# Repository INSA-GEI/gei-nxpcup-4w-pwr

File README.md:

# GEI NXP Cup — Carte puissance

Dépôt regroupant les fichiers de conception matérielle et logicielle de la carte de puissance du vehicule développé au département Génie Électrique et Informatique (GEI) de l'INSA Toulouse pour la compétition NXP Cup.

La carte de puissance est installée à l'arrière du véhicule. Elle assure la commande des actionneurs et la gestion de plusieurs périphériques du vehicule. Elle est construite autour d'un microcontrôleur **NXP MCXA153**.

## Fonctions de la carte

La carte de puissance assure les fonctions suivantes :

- **Commande des moteurs** de propulsion du véhicule.
- **Commande du servomoteur** de direction.
- **Mesure du niveau de batterie**, afin de surveiller l'alimentation du vehicule.
- **Commande des LED d'éclairage** du véhicule.
- **Connexion de périphériques I²C**.
- **Communication avec la carte principale** basée sur la FRDM-IMX8MP, via le bus I²C et une nappe de liaison.

La carte assure ainsi l'interface entre la carte principale, les actionneurs et les périphériques matériels du véhicule.

## Organisation du dépôt

Le dépôt est organisé en deux répertoires principaux.

| Répertoire | Contenu |
|---|---|
| [`hardware/`](hardware/) | Projet de conception électronique sous KiCad et nomenclature des composants (BOM) |
| [`software/`](software/) | Projet MCUXpresso IDE contenant le firmware en langage C destiné au microcontrôleur MCXA153 |

## 1. Conception matérielle — `hardware/`

Le répertoire `hardware/` contient les fichiers du projet KiCad utilisés pour concevoir la carte électronique de puissance.

Ils permettent notamment de consulter et de modifier le schéma électronique et le circuit imprimé (PCB).

La nomenclature des composants (**BOM — Bill of Materials**) est également fournie afin d'identifier les composants nécessaires à la fabrication de la carte.

### Outils nécessaires

- [KiCad](https://www.kicad.org/) : consultation et modification du schéma électronique et du circuit imprimé.
- Un outil de tableur peut être utilisé pour consulter la BOM, selon le format du fichier fourni.

Avant toute fabrication ou modification matérielle, vérifier la cohérence entre le schéma, le PCB, la nomenclature et la révision de carte utilisée sur le véhicule.

## 2. Firmware — `software/`

Le répertoire `software/` contient le projet **MCUXpresso IDE** et le code source C exécuté par le microcontrôleur NXP MCXA153.

Ce firmware assure les fonctions de commande de la carte de puissance et la communication avec la carte principale via le bus I²C.

### Outils nécessaires

- [MCUXpresso IDE](https://www.nxp.com/mcuxpresso) — version **26.2 ou supérieure**.
- Les composants logiciels et le SDK compatibles avec le projet et le microcontrôleur MCXA153.
- Une interface de programmation et de débogage compatible avec le matériel utilisé.

### Ouverture et compilation du projet

1. Installer MCUXpresso IDE dans une version compatible avec le projet.
2. Ouvrir l'environnement de développement et sélectionner un espace de travail (*workspace*).
3. Importer le projet présent dans le répertoire `software/`.
4. Vérifier que les composants logiciels et le SDK requis sont disponibles.
5. Compiler le projet et corriger les éventuelles erreurs de configuration.
6. Programmer le microcontrôleur avec le firmware compilé, en utilisant une interface de programmation compatible.

Les modalités exactes de programmation dépendent de la configuration matérielle et de l'interface de débogage utilisée.

## Ressources

- [NXP MCXA153 — informations produit et documentation](https://www.nxp.com/products/MCXA153)
- [MCUXpresso — environnement de développement NXP](https://www.nxp.com/mcuxpresso)
- [KiCad — logiciel de conception électronique](https://www.kicad.org/)

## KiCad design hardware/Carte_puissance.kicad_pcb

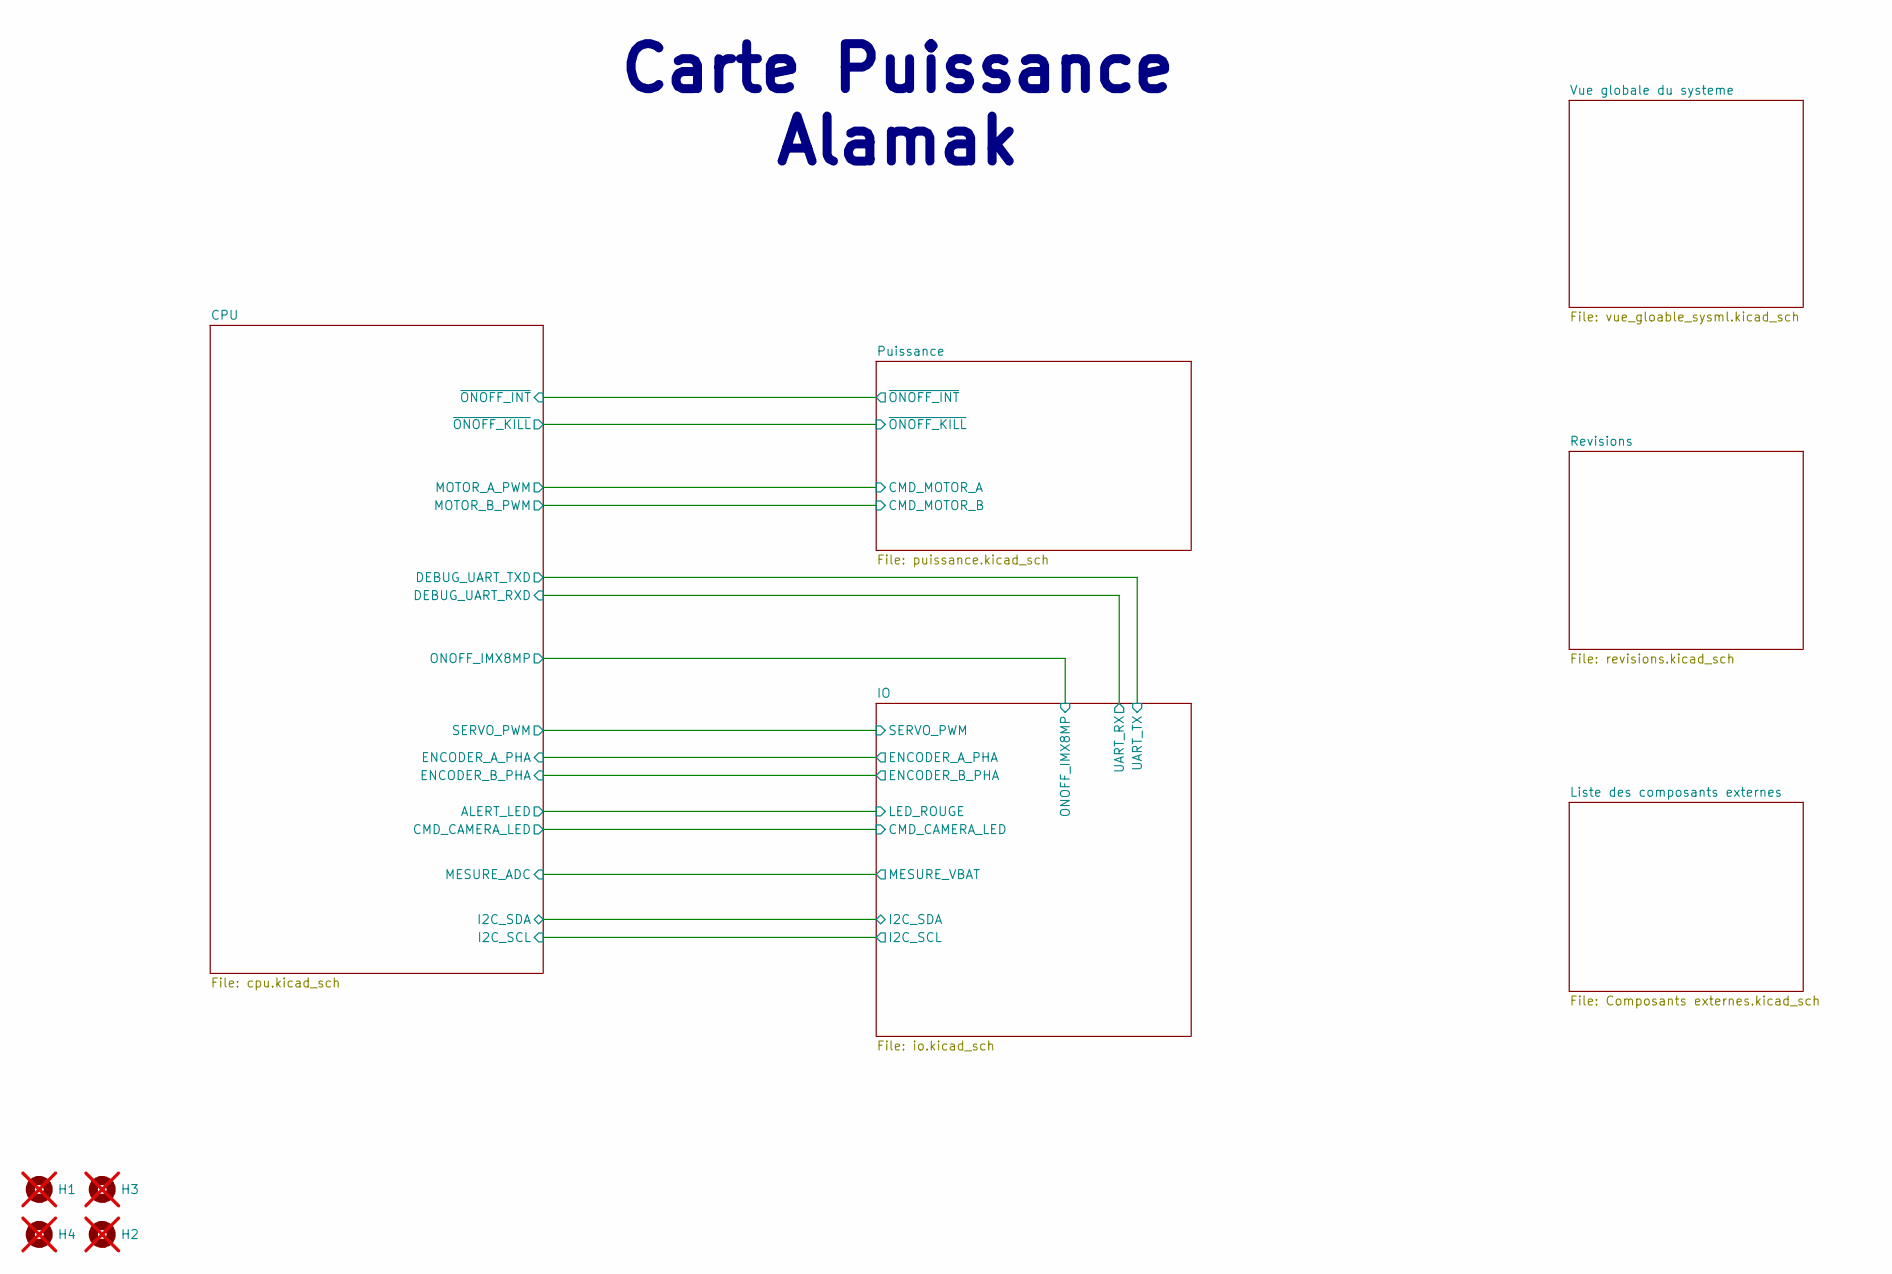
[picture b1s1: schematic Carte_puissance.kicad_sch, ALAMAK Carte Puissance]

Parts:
H1, H2, H3, H4: MountingHole; MountingHole_3.2mm_M3; not fitted

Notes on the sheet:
Carte Puissance Alamak

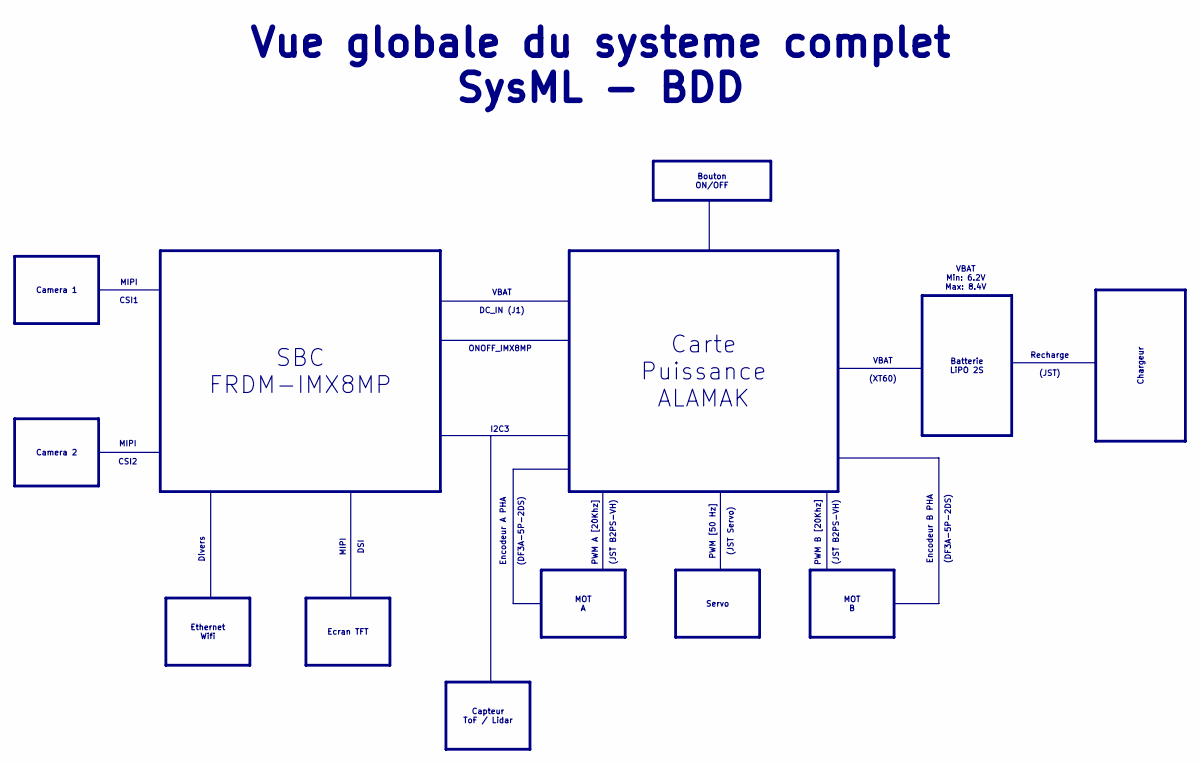
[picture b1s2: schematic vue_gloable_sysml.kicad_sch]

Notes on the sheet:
Chargeur
Servo
MOT A
MOT B
Ecran TFT
Batterie LiPO 2S
Capteur ToF / Lidar
Ethernet Wifi
SBC FRDM-IMX8MP
Camera 2
Camera 1
Carte Puissance ALAMAK
Bouton ON/OFF
PWM [50 Hz] (JST Servo)
VBAT Min: 6.2V Max: 8.4V
Vue globale du systeme complet SysML - BDD
Encodeur A PHA (DF3A-5P-2DS)
ONOFF_IMX8MP
PWM A [20Khz] (JST B2PS-VH)
MIPI CSI1
VBAT DC_IN (J1)
Divers
Recharge (JST)
VBAT (XT60)
Encodeur B PHA (DF3A-5P-2DS)
I2C3
MIPI CSI2
PWM B [20Khz] (JST B2PS-VH)
MIPI DSI

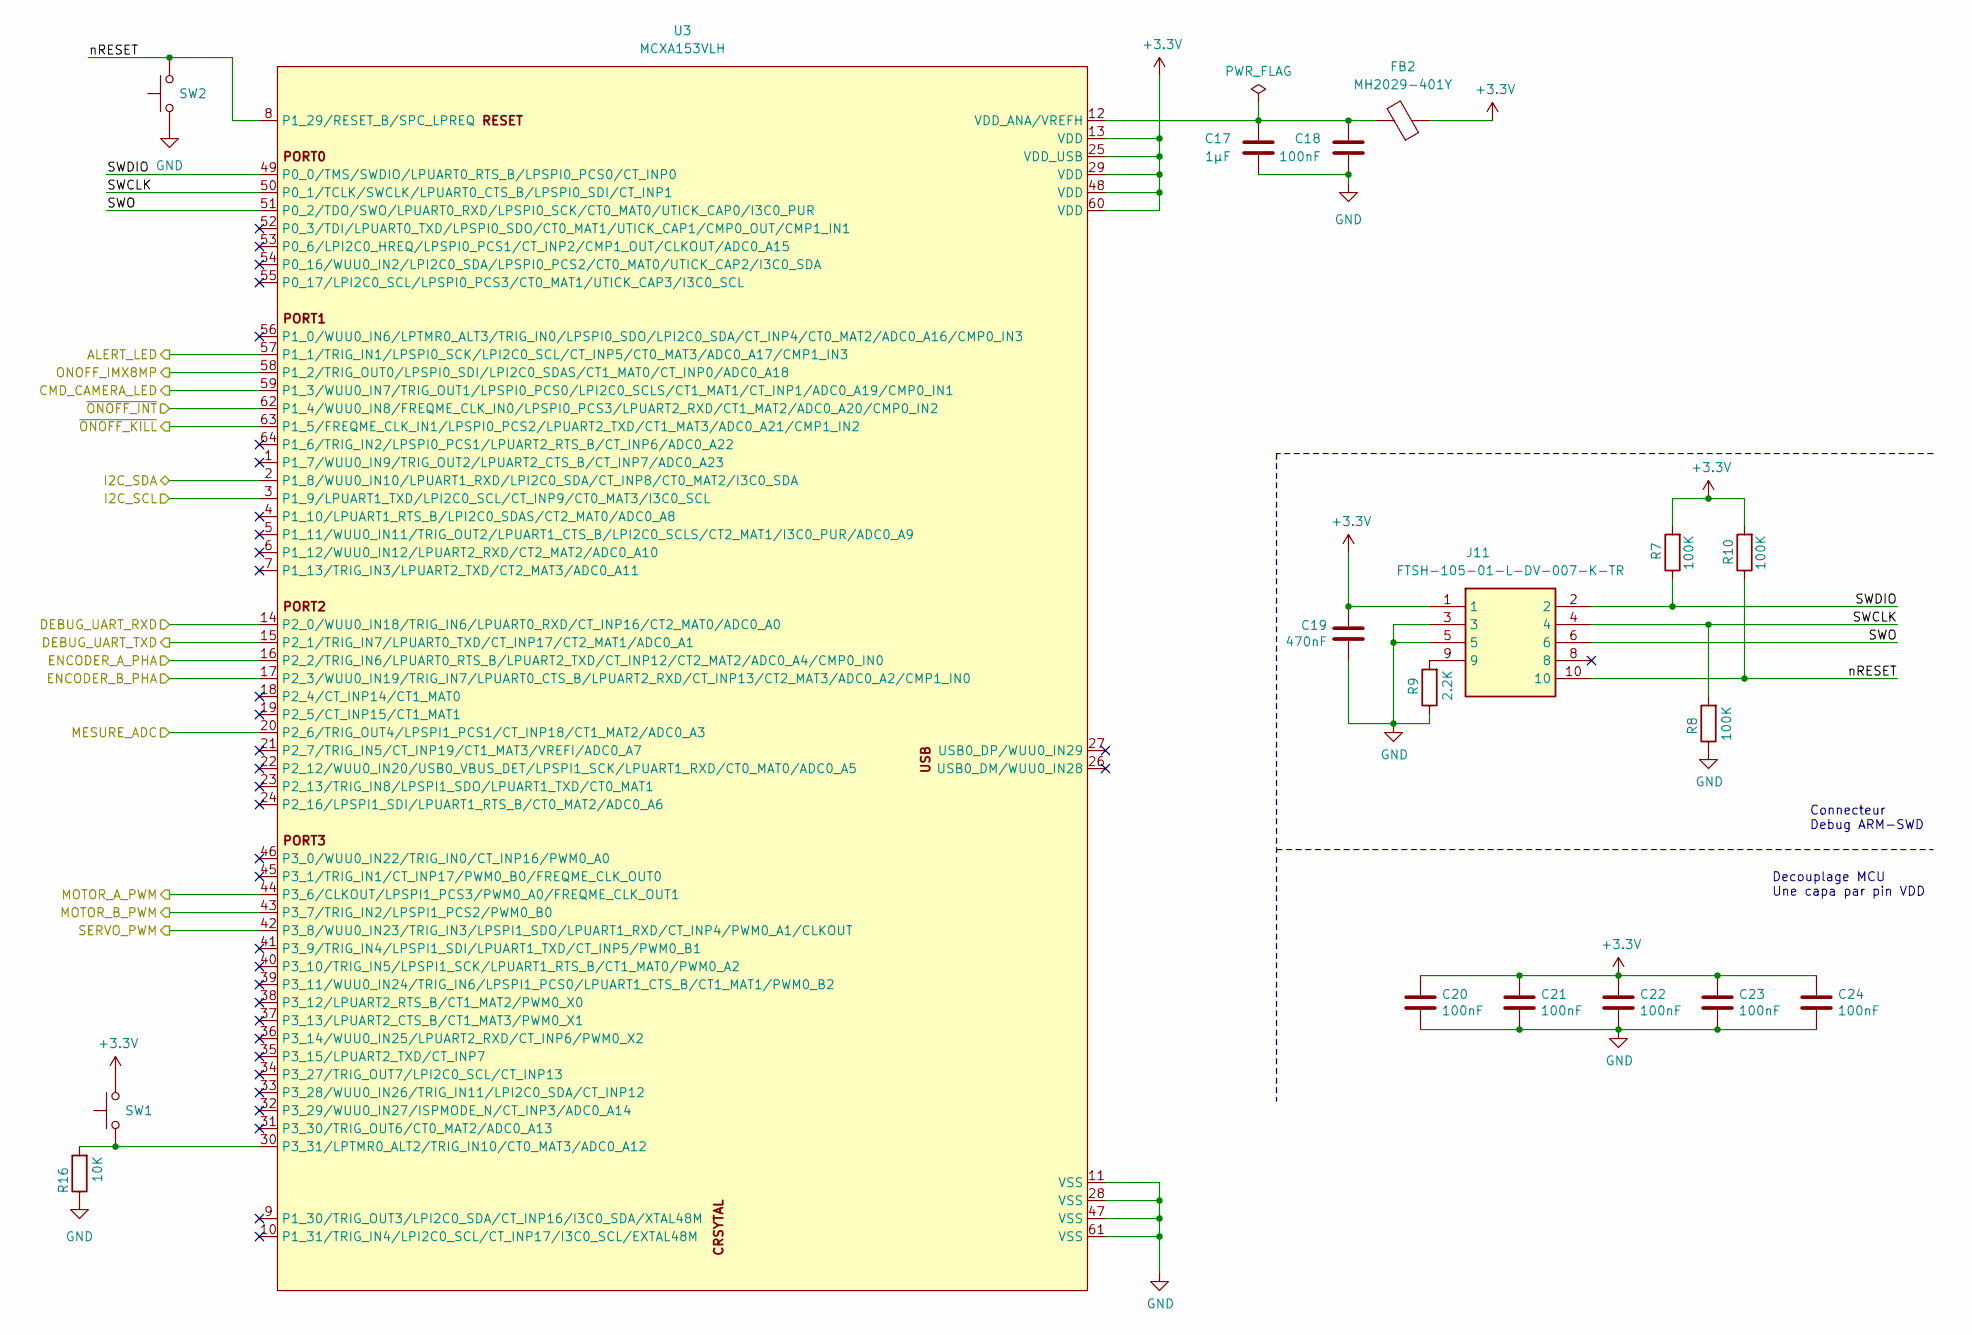
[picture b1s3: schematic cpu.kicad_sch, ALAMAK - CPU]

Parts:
C17: 1µF; C_0805_2012Metric; Part Number CL21B105KBFNNNF
C18, C20, C21, C22, C23, C24: 100nF; C_0805_2012Metric; Part Number CL21B104KBFNNNG
C19: 470nF; C_0805_2012Metric; Part Number CL21B474KBFNNNG
FB2: MH2029-401Y; C_0805_2012Metric_Pad1.18x1.45mm_HandSolder; Part Number MH2029-401Y
J11: FTSH-105-01-L-DV-007-K-TR; FTSH10501LDV007KTR; Part Number FTSH-105-01-L-DV-007-K-TR
R7, R8, R10: 100K; R_0805_2012Metric; Part Number RT0805FRE10100KL
R9: 2.2K; R_0805_2012Metric; Part Number RT0805FRE132K2L
R16: 10K; R_0805_2012Metric; Part Number RCA080510K0JNEASR
SW1, SW2: EVQ-P2602M; SW_SPST_EVQP2; Part Number EVQ-P2602M
U3: MCXA153VLH; LQFP-64_10x10mm_P0.5mm; Part Number MCXA153VLH

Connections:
+3.3V: C19.1, C20.1, C21.1, C22.1, C23.1, C24.1, FB2.1, J11.1, R7.2, R10.2, SW1.2, U3.13 (VDD), U3.25 (VDD_USB), U3.29 (VDD), U3.48 (VDD), U3.60 (VDD); also elsewhere on the board
/CPU/ALERT_LED: U3.57 (P1_1/TRIG_IN1/LPSPI0_SCK/LPI2C0_SCL/CT_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); also elsewhere on the board
/CPU/CMD_CAMERA_LED: U3.59 (P1_3/WUU0_IN7/TRIG_OUT1/LPSPI0_PCS0/LPI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); also elsewhere on the board
/CPU/DEBUG_UART_RXD: U3.14 (P2_0/WUU0_IN18/TRIG_IN6/LPUART0_RXD/CT_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); also elsewhere on the board
/CPU/DEBUG_UART_TXD: U3.15 (P2_1/TRIG_IN7/LPUART0_TXD/CT_INP17/CT2_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); also elsewhere on the board
/CPU/ENCODER_A_PHA: U3.16 (P2_2/TRIG_IN6/LPUART0_RTS_B/LPUART2_TXD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); also elsewhere on the board
/CPU/ENCODER_B_PHA: U3.17 (P2_3/WUU0_IN19/TRIG_IN7/LPUART0_CTS_B/L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); also elsewhere on the board
/CPU/I2C_SCL: U3.3 (P1_9/LPUART1_TXD/LPI2C0_SCL/CT_INP9/CT0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); also elsewhere on the board
/CPU/I2C_SDA: U3.2 (P1_8/WUU0_IN10/LPUART1_RXD/LPI2C0_SDA/C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); also elsewhere on the board
/CPU/MESURE_ADC: U3.20 (P2_6/TRIG_OUT4/LPSPI1_PCS1/CT_INP18/CT1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); also elsewhere on the board
/CPU/MOTOR_A_PWM: U3.44 (P3_6/CLKOUT/LPSPI1_PCS3/PWM0_A0/FREQME_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); also elsewhere on the board
/CPU/MOTOR_B_PWM: U3.43 (P3_7/TRIG_IN2/LPSPI1_PCS2/PWM0_B0); also elsewhere on the board
/CPU/ONOFF_IMX8MP: U3.58 (P1_2/TRIG_OUT0/LPSPI0_SDI/LPI2C0_SDAS/C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); also elsewhere on the board
/CPU/SERVO_PWM: U3.42 (P3_8/WUU0_IN23/TRIG_IN3/LPSPI1_SDO/LPUA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); also elsewhere on the board
/CPU/SWCLK: J11.4, R8.2, U3.50 (P0_1/TCLK/SWCLK/LPUART0_CTS_B/LPSPI0_SD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)
/CPU/SWDIO: J11.2, R7.1, U3.49 (P0_0/TMS/SWDIO/LPUART0_RTS_B/LPSPI0_PCS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)
/CPU/SWO: J11.6, U3.51 (P0_2/TDO/SWO/LPUART0_RXD/LPSPI0_SCK/CT0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)
/CPU/nRESET: J11.10, R10.1, SW2.2, U3.8 (P1_29/RESET_B/SPC_LPREQ)
/CPU/~ONOFF_INT: U3.62 (P1_4/WUU0_IN8/FREQME_CLK_IN0/LPSPI0_PCS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); also elsewhere on the board
/CPU/~ONOFF_KILL: U3.63 (P1_5/FREQME_CLK_IN1/LPSPI0_PCS2/LPUART2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); also elsewhere on the board
GND: C17.2, C18.2, C19.2, C20.2, C21.2, C22.2, C23.2, C24.2, J11.3, J11.5, R8.1, R9.1, R16.1, SW2.1, U3.11 (VSS), U3.28 (VSS), U3.47 (VSS), U3.61 (VSS); also elsewhere on the board
unnamed: J11.9, R9.2
unnamed: R16.2, SW1.1, U3.30 (P3_31/LPTMR0_ALT2/TRIG_IN10/CT0_MAT3/AD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)
unnamed: C17.1, C18.1, FB2.2, U3.12 (VDD_ANA/VREFH)

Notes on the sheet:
Decouplage MCU Une capa par pin VDD
Connecteur Debug ARM-SWD

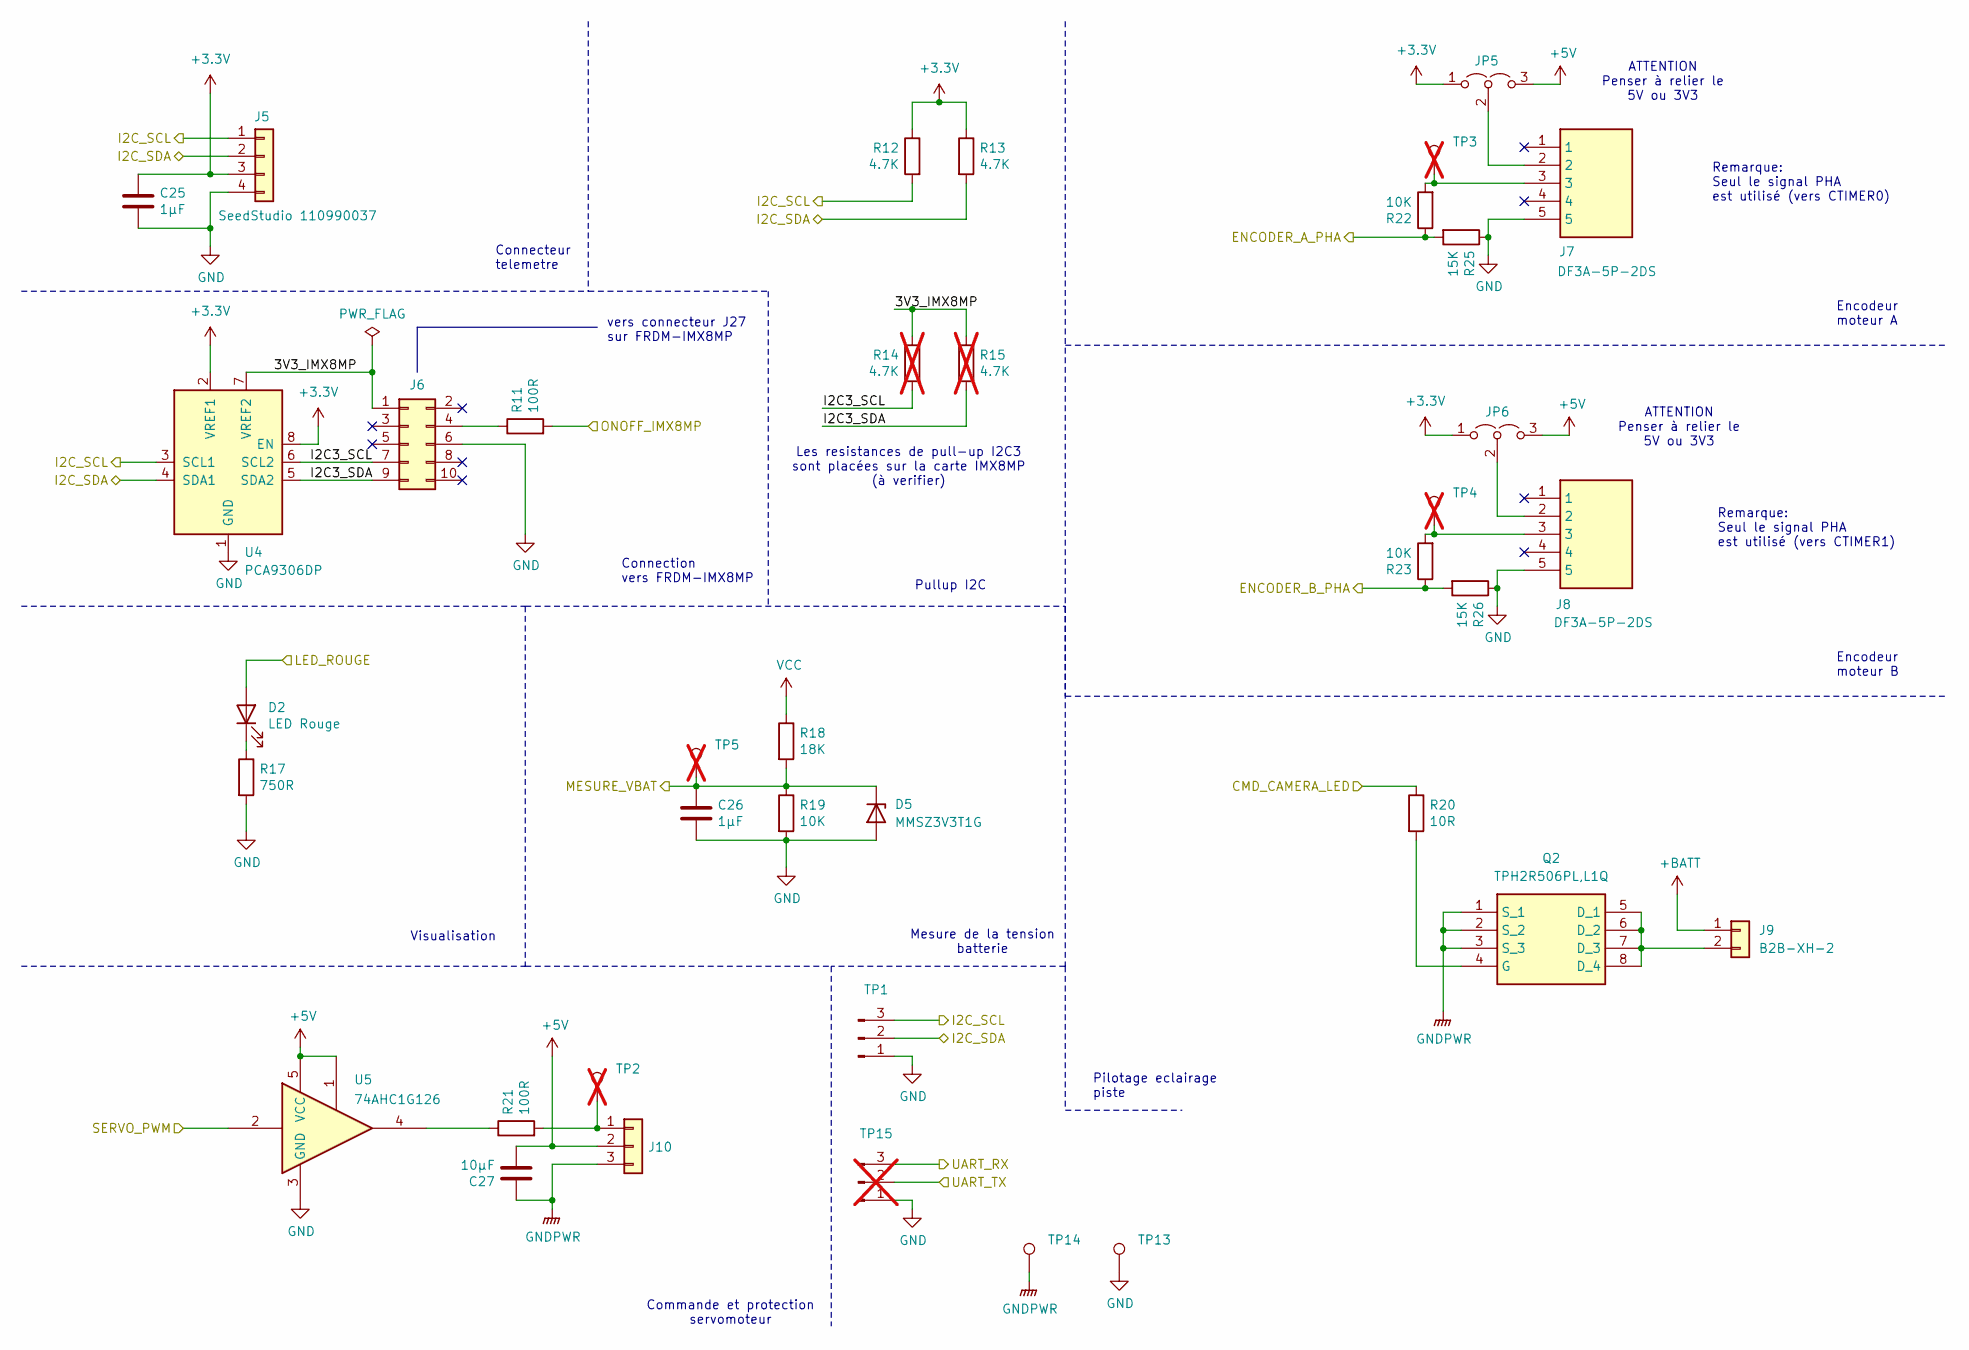
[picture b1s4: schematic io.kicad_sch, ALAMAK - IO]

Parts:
C25, C26: 1µF; C_0805_2012Metric; Part Number CL21B105KBFNNNF
C27: 10µF; C_0805_2012Metric; Part Number CGA4J1X7S1E106K125AE
D2: LED Rouge; LED_0805_2012Metric; Part Number APTD2012LSURCK
D5: MMSZ3V3T1G; D_SOD-123; Part Number MMSZ3V3T1G
J5: SeedStudio 110990037; SEEED_110990037; Part Number 110990037
J6: 72454-010VLF; IDC-Header_2x05_P2.54mm_Vertical_SMD; Part Number 72454-010VLF
J7, J8: DF3A-5P-2DS; SHDRRA5W60P0X200_1X5_1200X720X530P; Part Number DF3A-5P-2DS
J9: B2B-XH-2; JST_XH_B2B-XH-A_1x02_P2.50mm_Vertical; Part Number B2B-XH-2(LF)(SN)
J10: Cable Servomoteur JST; SolderWire-0.5sqmm_1x03_P4.8mm_D0.9mm_OD2.3mm; Part Number Cable JST Servo
JP5, JP6: Jumper_3_Open; SolderJumper-3_P1.3mm_Open_RoundedPad1.0x1.5mm
Q2: TPH2R506PL,L1Q; SOP-8_3.76x4.96mm_P1.27mm; Part Number TPH2R506PL,L1Q
R11, R21: 100R; R_0805_2012Metric; Part Number RT0805DRE07100RL
R12, R13: 4.7K; R_0805_2012Metric; Part Number RK73H2ATTD4701F
R14, R15: 4.7K; R_0805_2012Metric; Part Number RK73H2ATTD4701F; not fitted
R17: 750R; R_0805_2012Metric; Part Number RT0805BRD07750RL
R18: 18K; R_0805_2012Metric; Part Number RT0805FRE0718KL
R19, R22, R23: 10K; R_0805_2012Metric; Part Number RCA080510K0JNEASR
R20: 10R; R_0805_2012Metric; Part Number RT0805FRE1310RL
R25, R26: 15K; R_0805_2012Metric; Part Number RT0805DRE0715KL
TP1: TestPoint; PinHeader_1x03_P2.54mm_Vertical
TP2, TP3, TP4, TP5: TestPoint; PinHeader_1x01_P2.54mm_Vertical; not fitted
TP13, TP14: TestPoint; PinHeader_1x01_P2.54mm_Vertical
TP15: TestPoint; PinHeader_1x03_P2.54mm_Vertical; not fitted
U4: PCA9306DP; TSSOP-8_3x3mm_P0.65mm; Part Number PCA9306DP,118
U5: 74AHC1G126; SOT-23-5; Part Number SN74AHC1G126DBVR

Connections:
+3.3V: C25.1, J5.3, JP5.1 (A), JP6.1 (A), R12.1, R13.1, U4.2 (VREF1), U4.8 (EN); also elsewhere on the board
+5V: C27.2, J10.2, JP5.3 (B), JP6.3 (B), U5.1, U5.5 (VCC); also elsewhere on the board
+BATT: J9.1; also elsewhere on the board
/CPU/ALERT_LED: D2.2 (A); also elsewhere on the board
/CPU/CMD_CAMERA_LED: R20.1; also elsewhere on the board
/CPU/DEBUG_UART_RXD: TP15.3; also elsewhere on the board
/CPU/DEBUG_UART_TXD: TP15.2; also elsewhere on the board
/CPU/ENCODER_A_PHA: R22.1, R25.2; also elsewhere on the board
/CPU/ENCODER_B_PHA: R23.1, R26.2; also elsewhere on the board
/CPU/I2C_SCL: J5.1, R12.2, TP1.3, U4.3 (SCL1); also elsewhere on the board
/CPU/I2C_SDA: J5.2, R13.2, TP1.2, U4.4 (SDA1); also elsewhere on the board
/CPU/MESURE_ADC: C26.1, D5.1 (K), R18.2, R19.1, TP5.1; also elsewhere on the board
/CPU/ONOFF_IMX8MP: R11.2; also elsewhere on the board
/CPU/SERVO_PWM: U5.2; also elsewhere on the board
/IO/3V3_IMX8MP: J6.1, R14.1, R15.1, U4.7 (VREF2)
/IO/I2C3_SCL: J6.7, R14.2, U4.6 (SCL2)
/IO/I2C3_SDA: J6.9, R15.2, U4.5 (SDA2)
GND: C25.2, C26.2, D5.2 (A), J5.4, J6.6, J7.5, J8.5, R17.2, R19.2, R25.1, R26.1, TP1.1, TP13.1, TP15.1, U4.1 (GND), U5.3 (GND); also elsewhere on the board
GNDPWR: C27.1, J10.3, Q2.1 (S_1), Q2.2 (S_2), Q2.3 (S_3), TP14.1; also elsewhere on the board
unnamed: D2.1 (K), R17.1
unnamed: J6.4, R11.1
unnamed: J7.3, R22.2, TP3.1
unnamed: J8.3, R23.2, TP4.1
unnamed: J9.2, Q2.5 (D_1), Q2.6 (D_2), Q2.7 (D_3), Q2.8 (D_4)
unnamed: J10.1, R21.2, TP2.1
unnamed: J7.2, JP5.2 (C)
unnamed: J8.2, JP6.2 (C)
unnamed: Q2.4 (G), R20.2
unnamed: R21.1, U5.4
VCC: R18.1; also elsewhere on the board

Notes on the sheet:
Connecteur telemetre
ATTENTION Penser à relier le 5V ou 3V3
Mesure de la tension batterie
Remarque: Seul le signal PHA est utilisé (vers CTIMER0)
Visualisation
Connection vers FRDM-IMX8MP
Encodeur moteur B
Pilotage eclairage piste
vers connecteur J27 sur FRDM-IMX8MP
Les resistances de pull-up I2C3 sont placées sur la carte IMX8MP (à verifier)
Commande et protection servomoteur
Encodeur moteur A
Remarque: Seul le signal PHA est utilisé (vers CTIMER1)
Pullup I2C

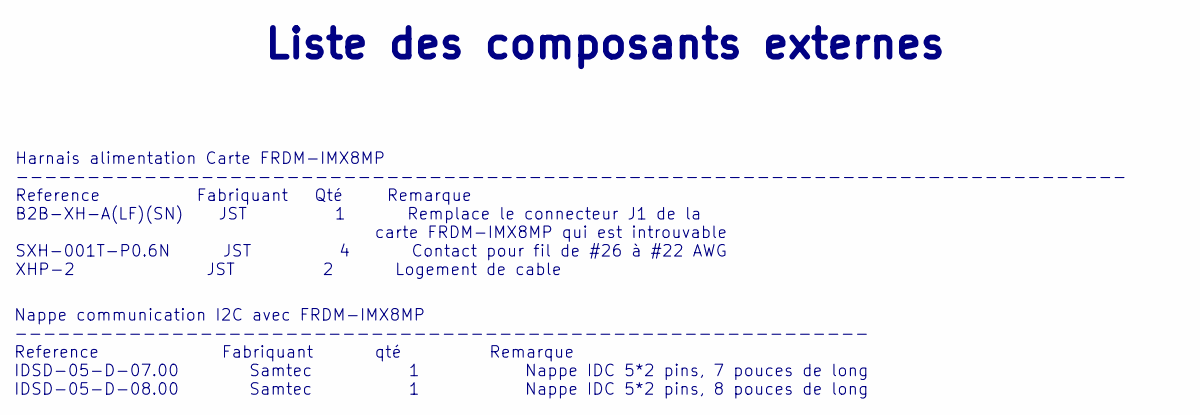
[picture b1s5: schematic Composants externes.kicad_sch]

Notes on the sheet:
Harnais alimentation Carte FRDM-IMX8MP ------------------------------------------------------------------------------ Reference Fabriquant Qté Remarque B2B-XH-A(LF)(SN) JST 1 Remplace le connecteur J1 de la carte FRDM-IMX8MP qui est introuvable SXH-001T-P0.6N JST 4 Contact pour fil de #26 à #22 AWG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
Nappe communication I2C avec FRDM-IMX8MP ------------------------------------------------------------ Reference Fabriquant qté Remarque IDSD-05-D-07.00 Samtec 1 Nappe IDC 5*2 pins, 7 pouces de long IDSD-05-D-08.00 Samtec 1 Nappe IDC 5*2 pins, 8 pouces de long
Liste des composants externes

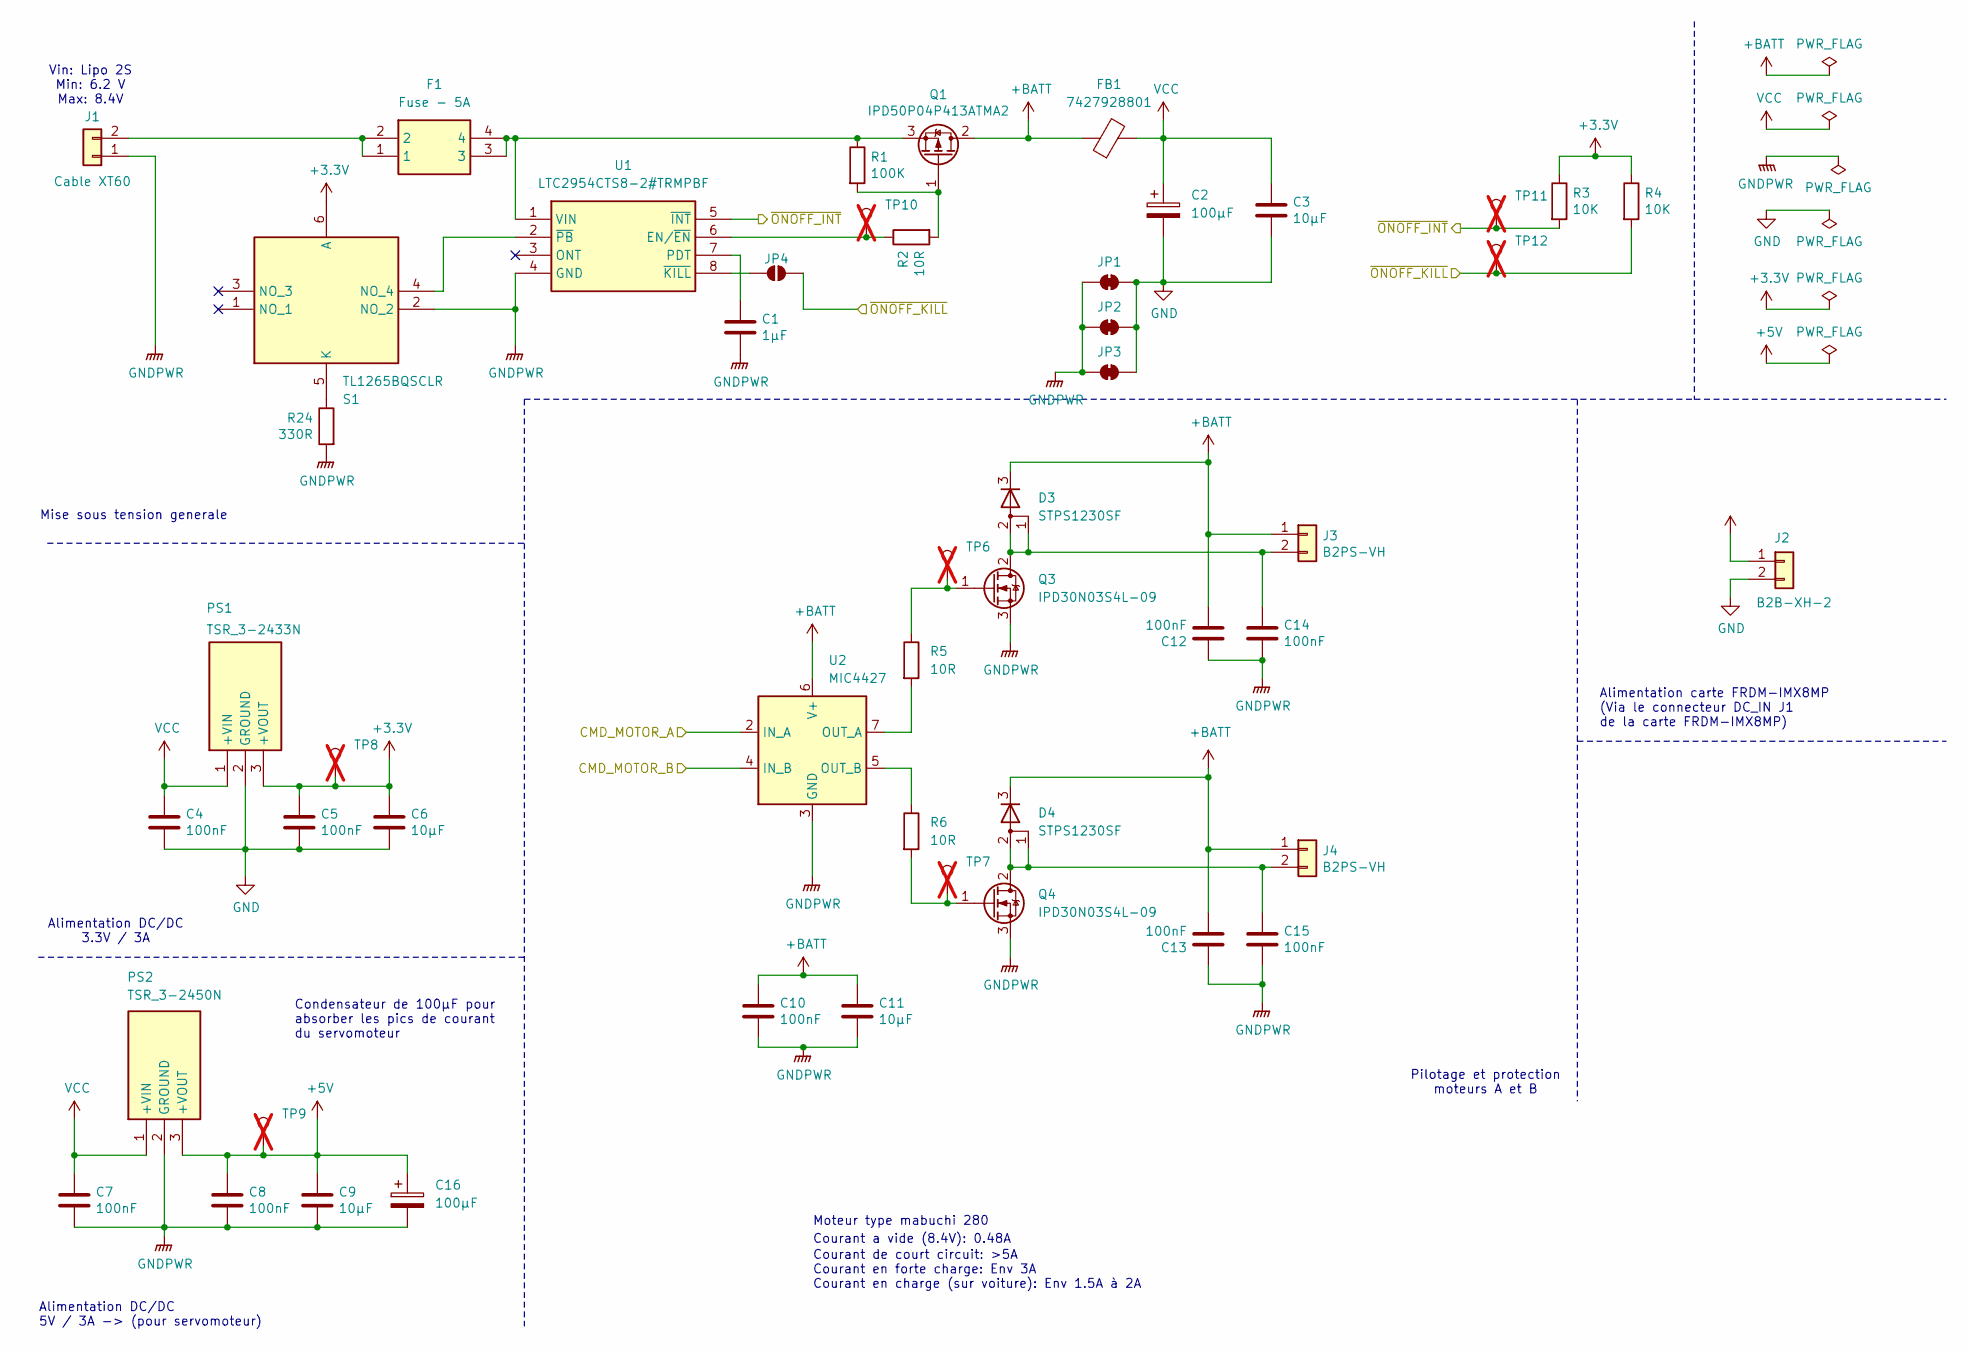
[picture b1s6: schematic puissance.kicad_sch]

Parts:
C1: 1µF; C_0805_2012Metric; Part Number CL21B105KBFNNNF
C2, C16: 100µF; CP_Elec_10x10; Part Number EMVH500ARA101MJA0G
C3, C6, C9, C11: 10µF; C_0805_2012Metric; Part Number CGA4J1X7S1E106K125AE
C4, C5, C7, C8, C10, C12, C13, C14, C15: 100nF; C_0805_2012Metric; Part Number CL21B104KBFNNNG
D3, D4: STPS1230SF; TO-277A; Part Number STPS1230SF
F1: Fuse - 5A; 3568; Part Number 3568
FB1: 7427928801; C_2220_5750Metric; Part Number 7427928801
J1: Cable XT60; Battery_Pads; Part Number Cable batterie XT60
J2: B2B-XH-2; JST_XH_B2B-XH-A_1x02_P2.50mm_Vertical; Part Number B2B-XH-2(LF)(SN)
J3, J4: B2PS-VH; JST_VH_B2PS-VH_1x02_P3.96mm_Horizontal; Part Number B2PS-VH(LF)(SN)
JP1, JP2, JP3: SolderJumper_2_Bridged; SolderJumper-2_P1.3mm_Bridged2Bar_RoundedPad1.0x1.5mm
JP4: SolderJumper_2_Open; SolderJumper-2_P1.3mm_Open_RoundedPad1.0x1.5mm
PS1: TSR_3-2433N; TSR324xxN; Part Number TSR_3-2433N
PS2: TSR_3-2450N; TSR324xxN; Part Number TSR_3-2450N
Q1: IPD50P04P413ATMA2; TO-252-2; Part Number IPD50P04P413ATMA2
Q3, Q4: IPD30N03S4L-09; TO-252-2; Part Number IPD30N03S4L-09
R1: 100K; R_0805_2012Metric; Part Number RT0805FRE10100KL
R2, R5, R6: 10R; R_0805_2012Metric; Part Number RT0805FRE1310RL
R3, R4: 10K; R_0805_2012Metric; Part Number RCA080510K0JNEASR
R24: 330R; R_0805_2012Metric; Part Number RT0805DRD07330RL
S1: TL1265BQSCLR; Mouser Part Number 612-TL1265BQSCLR
TP6, TP7, TP8, TP9, TP10, TP11, TP12: TestPoint; PinHeader_1x01_P2.54mm_Vertical; not fitted
U1: LTC2954CTS8-2#TRMPBF; SOT-23-8; Part Number LTC2954CTS8-2#TRPBF
U2: MIC4427; SO-8_3.9x4.9mm_P1.27mm; Part Number MIC4427ZM

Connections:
+3.3V: C5.1, C6.1, PS1.3 (+VOUT), R3.1, R4.1, S1.6 (A), TP8.1; also elsewhere on the board
+5V: C8.1, C9.1, C16.1, PS2.3 (+VOUT), TP9.1; also elsewhere on the board
+BATT: C10.1, C11.1, C12.2, C13.2, D3.3 (K), D4.3 (K), FB1.1, J3.1, J4.1, Q1.2 (D), U2.6 (V+); also elsewhere on the board
/CPU/MOTOR_A_PWM: U2.2 (IN_A); also elsewhere on the board
/CPU/MOTOR_B_PWM: U2.4 (IN_B); also elsewhere on the board
/CPU/~ONOFF_INT: R3.2, TP11.1, U1.5 (~INT); also elsewhere on the board
/CPU/~ONOFF_KILL: JP4.2 (B), R4.2, TP12.1; also elsewhere on the board
GND: C2.2, C3.2, C4.2, C5.2, C6.2, J2.2, JP1.2 (B), JP2.2 (B), JP3.2 (B), PS1.2 (GROUND); also elsewhere on the board
GNDPWR: C1.2, C7.2, C8.2, C9.2, C10.2, C11.2, C12.1, C13.1, C14.2, C15.2, C16.2, J1.1, JP1.1 (A), JP2.1 (A), JP3.1 (A), PS2.2 (GROUND), Q3.3 (S), Q4.3 (S), R24.2, S1.2 (NO_2), U1.4 (GND), U2.3 (GND); also elsewhere on the board
unnamed: F1.1, F1.2, J1.2
unnamed: C14.1, D3.1 (A), D3.2 (A), J3.2, Q3.2 (D)
unnamed: C15.1, D4.1 (A), D4.2 (A), J4.2, Q4.2 (D)
unnamed: JP4.1 (A), U1.8 (~KILL)
unnamed: Q1.1 (G), R1.2, R2.2
unnamed: F1.3, F1.4, Q1.3 (S), R1.1, U1.1 (VIN)
unnamed: Q3.1 (G), R5.1, TP6.1
unnamed: Q4.1 (G), R6.2, TP7.1
unnamed: R24.1, S1.5 (K)
unnamed: S1.4 (NO_4), U1.2 (~PB)
unnamed: R2.1, TP10.1, U1.6 (EN/~EN)
unnamed: C1.1, U1.7 (PDT)
unnamed: R5.2, U2.7 (OUT_A)
unnamed: R6.1, U2.5 (OUT_B)
VCC: C2.1, C3.1, C4.1, C7.1, FB1.2, J2.1, PS1.1 (+VIN), PS2.1 (+VIN); also elsewhere on the board

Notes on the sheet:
Alimentation DC/DC 3.3V / 3A
Alimentation carte FRDM-IMX8MP (Via le connecteur DC_IN J1 de la carte FRDM-IMX8MP)
Mise sous tension generale
Vin: Lipo 2S Min: 6.2 V Max: 8.4V
Courant de court circuit: >5A Courant en forte charge: Env 3A Courant en charge (sur voiture): Env 1.5A à 2A
Condensateur de 100µF pour absorber les pics de courant du servomoteur
Alimentation DC/DC 5V / 3A -> (pour servomoteur)
Moteur type mabuchi 280
Courant a vide (8.4V): 0.48A
Pilotage et protection moteurs A et B

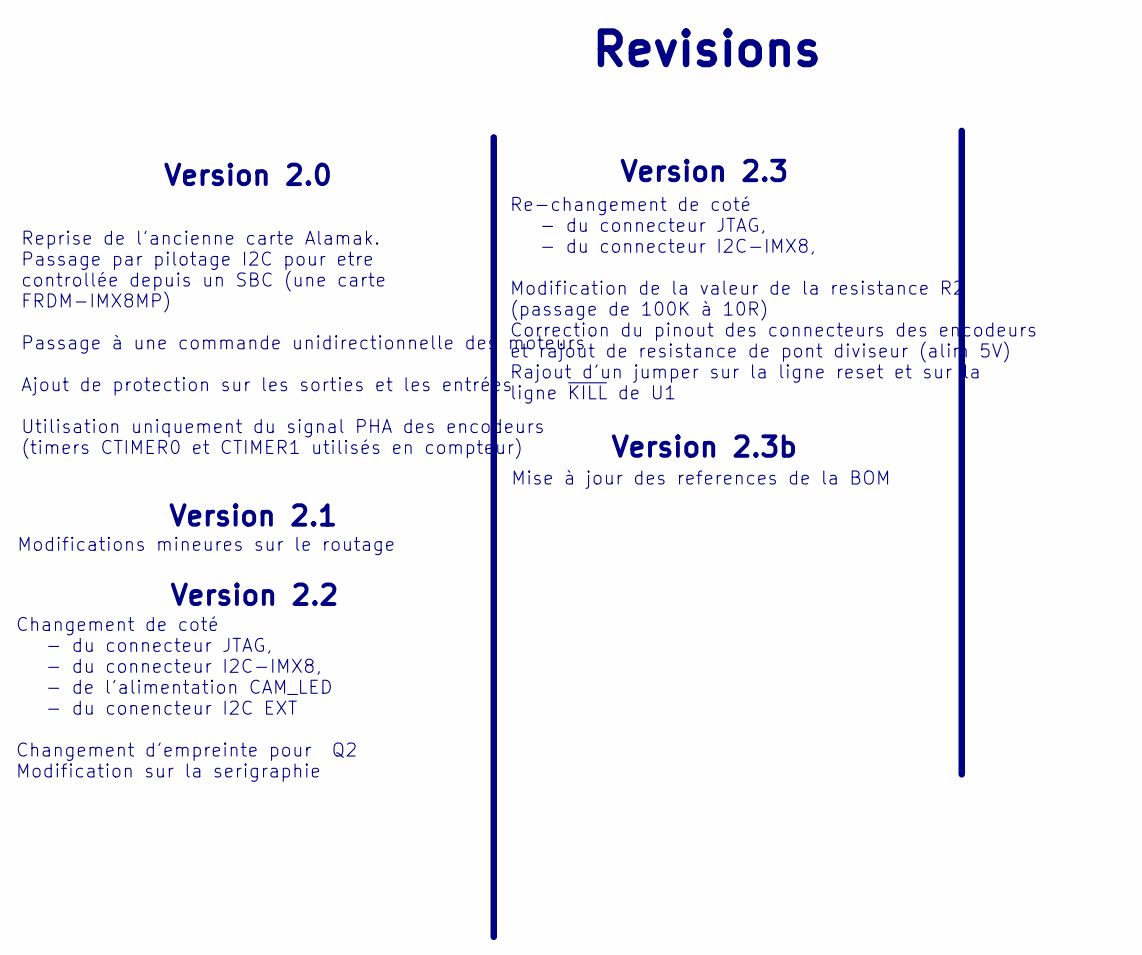
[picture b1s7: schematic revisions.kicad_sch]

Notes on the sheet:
Version 2.2
Mise à jour des references de la BOM
Version 2.3b
Version 2.1
Modifications mineures sur le routage
Version 2.3
Re-changement de coté - du connecteur JTAG, - du connecteur I2C-IMX8, Modification de la valeur de la resistance R2 (passage de 100K à 10R) Correction du pinout des connecteurs des encodeurs et rajout de resistance de pont diviseur (alim 5V) Rajout d'un jumper sur la ligne reset et sur la ligne ~{K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
Reprise de l'ancienne carte Alamak. Passage par pilotage I2C pour etre controllée depuis un SBC (une carte FRDM-IMX8MP) Passage à une commande unidirectionnelle des moteurs Ajout de protection sur les sorties et les entrées Utilisation uniquement du signal PHA des encodeurs (timers CTIMER0 et CTIME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
Version 2.0
Changement de coté - du connecteur JTAG, - du connecteur I2C-IMX8, - de l'alimentation CAM_LED - du conencteur I2C EXT Changement d'empreinte pour Q2 Modification sur la serigraphie
Revisions

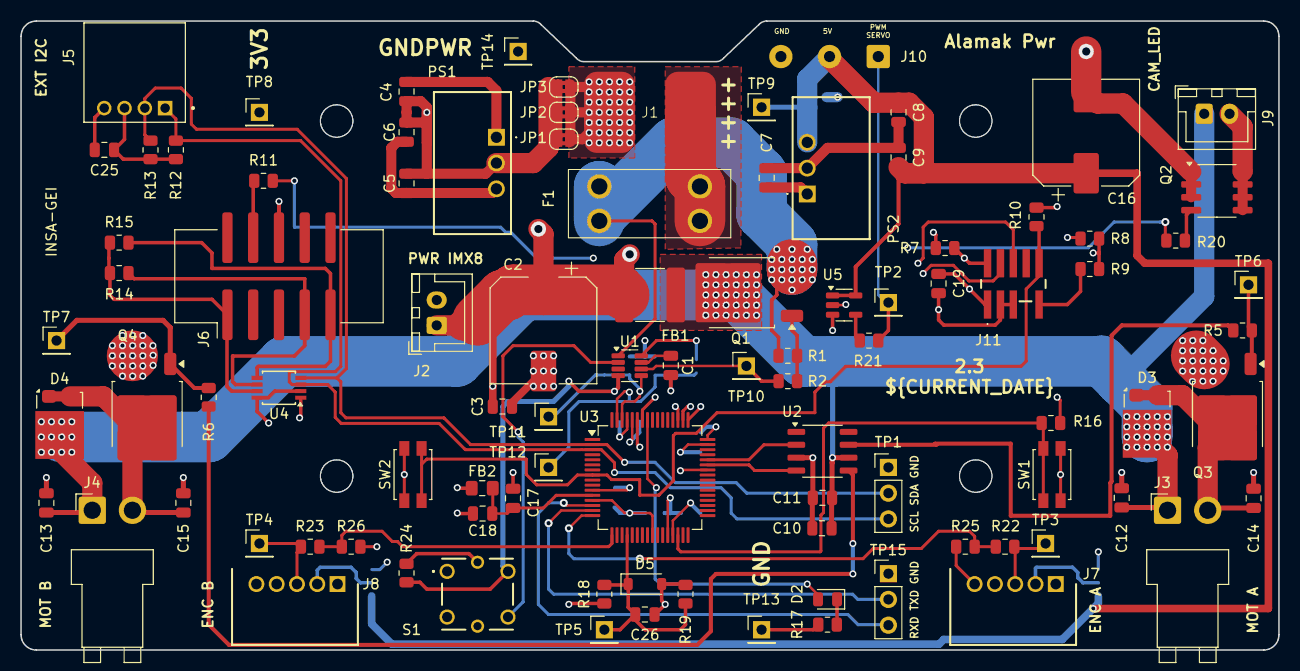
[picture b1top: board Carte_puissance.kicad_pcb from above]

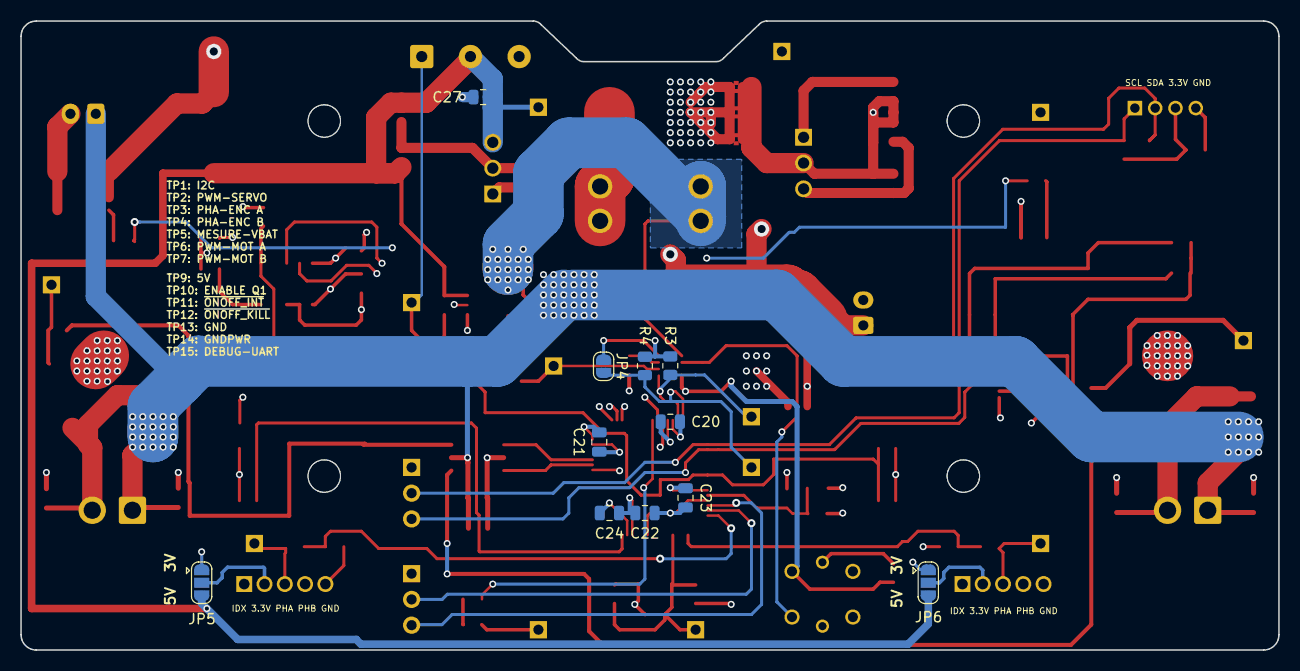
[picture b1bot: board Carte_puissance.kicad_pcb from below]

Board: 4 copper layers, 124.0 x 62.0 mm, 110 parts (11 on the bottom side), 55 nets.

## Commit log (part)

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2026-05-13 Initial plan
2026-05-13 chore: add KiCad ignores, LFS attributes, and project directories
    Agent-Logs-Url: https://github.com/INSA-GEI/gei-nxpcup-4w-pwr/sessions/bccda065-d94e-435e-a597-74c599226170
2026-05-21 WIP schema terminé, empreintes de composants verifié, reste à faire les verifications
2026-05-27 Wip carte alamk pwr 2.0 prete pour tirage
2026-05-28 Wip correction sur le connecteur debug et realisation d'un soft de test pour verifier le mapping des fonctions sur les pins
2026-06-19 Code MCXA153 en cours de dev, les fonctions sont gobalement implementées
